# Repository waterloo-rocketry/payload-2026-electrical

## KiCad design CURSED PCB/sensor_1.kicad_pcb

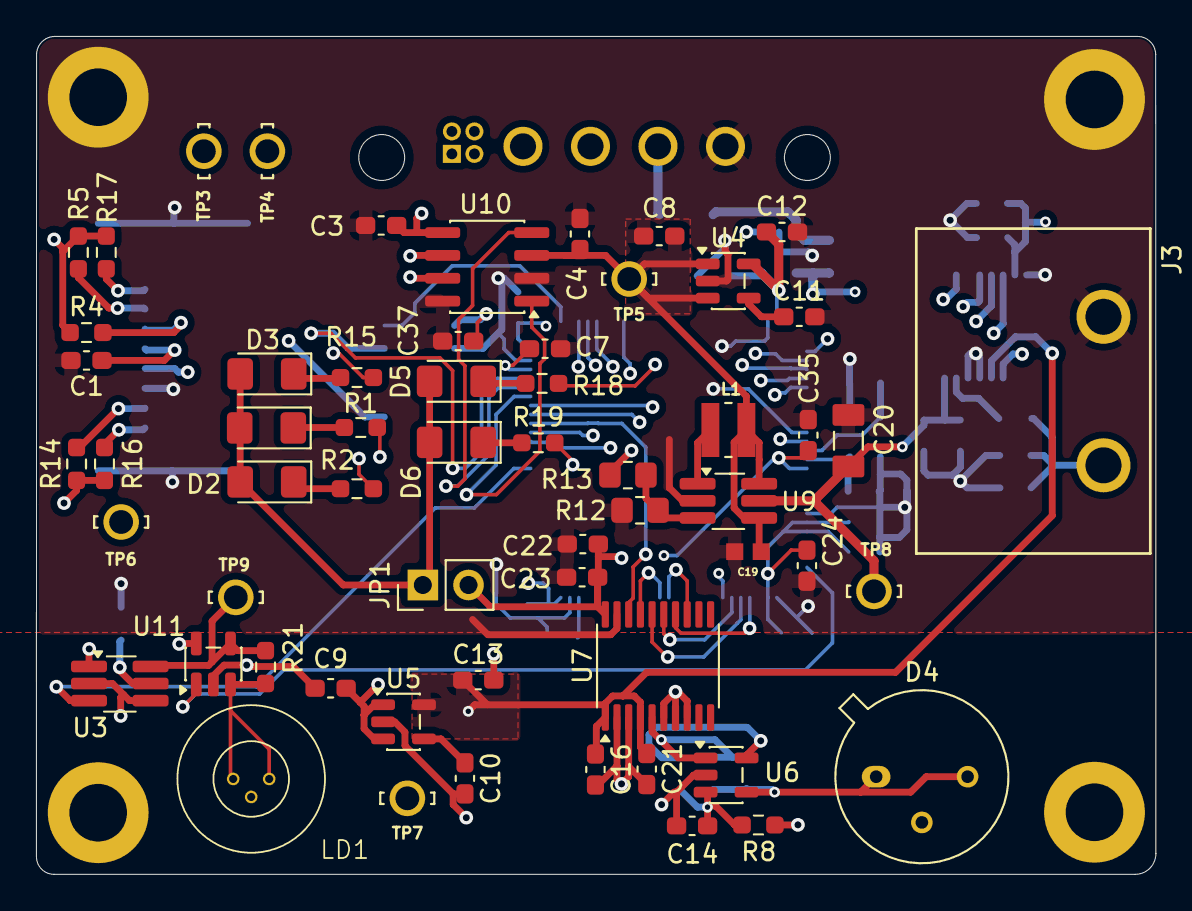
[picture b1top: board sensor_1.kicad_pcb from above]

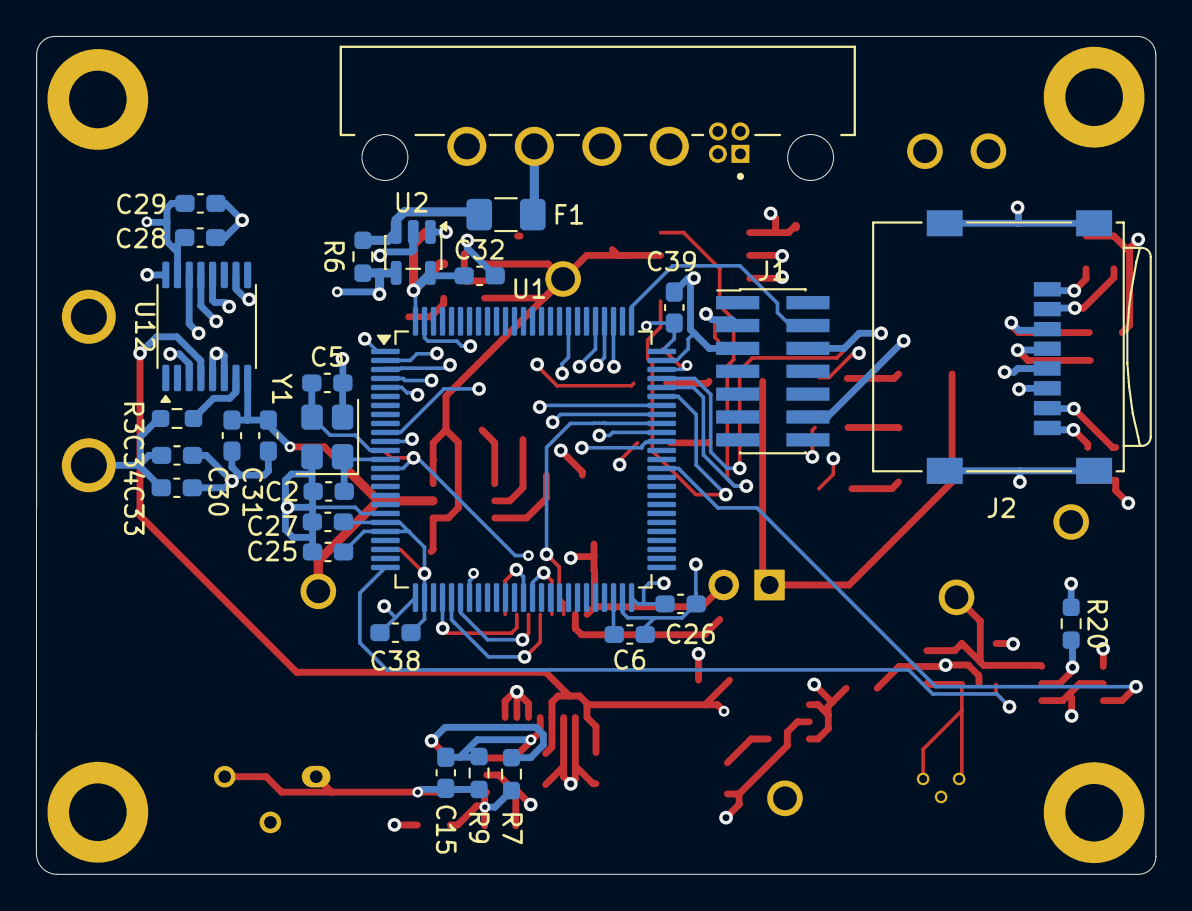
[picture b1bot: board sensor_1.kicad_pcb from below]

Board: 4 copper layers, 62.2 x 46.5 mm, 92 parts (29 on the bottom side), 58 nets.

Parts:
C1, C3, C4, C16, C22, C32: 0.1uF; C_0603_1608Metric_Pad1.08x0.95mm_HandSolder
C2, C5: 6pF; C_0603_1608Metric_Pad1.08x0.95mm_HandSolder
C6, C7: 2.2uF; C_0603_1608Metric_Pad1.08x0.95mm_HandSolder
C8, C9, C12, C13, C25, C26, C27, C35, C37, C38, C39: 1uF; C_0603_1608Metric_Pad1.08x0.95mm_HandSolder
C10, C11: 10nF; C_0603_1608Metric_Pad1.08x0.95mm_HandSolder
C14: 0.1u; C_0603_1608Metric_Pad1.08x0.95mm_HandSolder
C15: 6500nF; C_0603_1608Metric_Pad1.08x0.95mm_HandSolder
C19: 1uF; CAPC1608X90N
C20: 4.75uF; CAPC3216X180N
C21, C23, C29, C31, C34: 10uF; C_0603_1608Metric_Pad1.08x0.95mm_HandSolder
C24: 4.7uF; C_0603_1608Metric_Pad1.08x0.95mm_HandSolder
C28, C30: 100nF; C_0603_1608Metric_Pad1.08x0.95mm_HandSolder
C33: 100uF; C_0603_1608Metric_Pad1.08x0.95mm_HandSolder
D1, D3, D5, D6: BLUE LED; LED_1206_3216Metric_Pad1.42x1.75mm_HandSolder
D2: RED LED; LED_1206_3216Metric_Pad1.42x1.75mm_HandSolder
D4: ODD-5WISOL; TO-5-3
F1: 1A; Fuse_1206_3216Metric_Pad1.42x1.75mm_HandSolder
H1: MH1; MountingHole_3.2mm_M3_DIN965_Pad
H2: MH2; MountingHole_3.2mm_M3_DIN965_Pad
H3: MH3; MountingHole_3.2mm_M3_DIN965_Pad
H4: MH4; MountingHole_3.2mm_M3_DIN965_Pad
J1: Debugging Connector; PinHeader_2x07_P1.27mm_Vertical_SMD
J2: Micro_SD_Card; microSD_Molex_WM6698CT-ND
J3: Conn_01x02_Pin; BarrierBlock_ED2945-ND
J5: G125-MH104M4-04AD000P; connector_Harwin_G125-MH104M4-04AD000P
JP1: Jumper; PinHeader_1x02_P2.54mm_Vertical
L1: VLS3012CX-100M-1; IND_VLS3012CX-100M-1
LD1: D_Laser_Photo_PType; L840P200
R1, R2, R15, R18, R19: 220R; R_0603_1608Metric_Pad0.98x0.95mm_HandSolder
R3: 0R; R_0603_1608Metric_Pad0.98x0.95mm_HandSolder
R4, R5, R14, R16, R17: 10k; R_0603_1608Metric_Pad0.98x0.95mm_HandSolder
R6, R21: 33m; R_0603_1608Metric_Pad0.98x0.95mm_HandSolder
R7: 13.7k; R_0603_1608Metric_Pad0.98x0.95mm_HandSolder
R8: 280; R_0603_1608Metric_Pad0.98x0.95mm_HandSolder
R9: 128; R_0603_1608Metric_Pad0.98x0.95mm_HandSolder
R12: 71.5K; R_0805_2012Metric_Pad1.20x1.40mm_HandSolder
R13: 2.76M; R_0805_2012Metric_Pad1.20x1.40mm_HandSolder
R20: CALCUATE; R_0603_1608Metric_Pad0.98x0.95mm_HandSolder
TP3, TP4, TP5, TP6, TP7, TP8, TP9: 4952; KEYSTONE_4952
U1: STM32H750VBT6TR; LQFP-100_14x14mm_P0.5mm
U2, U11: INA180-A3; SOT-23-5
U3: AP22653AW6-7; TSOT-23-6_HandSoldering
U4, U5: SPX3819M5-L-3-3; SOT-23-5
U6: OPA323; SOT-23-5
U7: MCP3562-E_ST; TSSOP-20_4.4x6.5mm_P0.65mm
U9: TLV61046ADBVR; TSOT-23-6_HandSoldering
U10: MCP2562; SOIC-8_3.9x4.9mm_P1.27mm
U12: AD5761BRUZ; TSSOP-16_4.4x5mm_P0.65mm
Y1: 24MHz crystal; Crystal_SMD_Abracon_ABM8G-4Pin_3.2x2.5mm

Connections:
+3.3VA: C13.1, C16.1, C21.1, TP7.TP, U3.1 (IN), U5.5 (OUT), U7.1 (AVDD), U7.4 (REFIN+), U11.5 (V+), U12.4 (VREFIN)
+3.3VD: C1.1, C3.2, C12.1, C22.1, C23.1, C24.2, C25.2, C26.2, C27.2, C28.2, C29.2, C32.1, C37.2, C38.2, C39.2, J1.3, J2.4 (VDD), JP1.2 (B), R4.1, R5.1, R14.1, R16.1, R17.1, TP6.TP, U1.11 (VDD), U1.20 (VREF+), U1.21 (VDDA), U1.27 (VDD), U1.50 (VDD), U1.75 (VDD), U1.100 (VDD), U2.5 (V+), U4.5 (OUT), U7.20 (DVDD), U10.5 (VIO), U12.15 (DVCC)
+5V: C4.1, C8.1, C9.1, C19.1, L1.1, R6.2, R7.2, TP5.TP, U2.4 (-), U4.1 (IN), U4.3 (EN), U5.1 (IN), U5.3 (EN), U6.5 (V+), U9.4 (EN), U9.6 (VIN), U10.3 (VDD)
+24V: C20.1, C30.2, C31.2, R13.2, TP8.TP, U9.5 (VOUT), U12.8 (VDD)
/CS_ADC: U1.38 (PE8), U7.13 (~CS)
/CUR_SEN: U1.32 (PC4), U2.1
/IRQ/MDAT: U1.39 (PE9), U7.17 (~IRQ/MDAT)
/LAS_SENSE: U1.25 (PA3), U11.1
/Laser/Las_enable: U1.62 (PD15), U3.3 (EN/*EN)
/MCLR: C35.2, J1.12, U1.14 (NRST)
/MCU/CS_DAC: U1.69 (PA10), U12.13 (~SYNC)
/MCU/DAC_RESET: U1.68 (PA9), U12.3 (~RESET)
/MCU/OCS1/CLKIN: C5.1, U1.12 (PH0-OSC_IN), Y1.3
/MCU/OCS2/CLKOUT: C2.2, U1.13 (PH1-OSC_OUT), Y1.1
/MISO: U1.30 (PA6), U7.16 (SDO), U12.12 (SDI)
/MKLKIN: U1.67 (PA8), U7.18 (MCLKIN)
/MOSI: U1.31 (PA7), U7.15 (SDI), U12.10 (SDO)
/PGC/ICSPDAT: J1.4, U1.76 (PA14)
/PGD/ICSPCLK: J1.6, U1.72 (PA13)
/PZT: C33.2, C34.2, J3.1, R3.2
/Power/CANH: J5.1 (CANH), TP3.TP, U10.7 (CANH)
/Power/CANL: J5.2 (CANL), TP4.TP, U10.6 (CANL)
/RXD: U1.71 (PA12), U10.4 (RXD)
/SCLK: U1.29 (PA5), U7.14 (SCK), U12.14 (SCLK)
/SD_CS: J2.3 (CMD), R4.2, U1.83 (PD2)
/SD_DATA0: J2.7 (DAT0), R14.2, U1.65 (PC8)
/SD_DATA1: J2.8 (DAT1), R16.2, U1.66 (PC9)
/SD_DATA2: J2.1 (DAT2), R17.2, U1.78 (PC10)
/SD_DATA3: J2.2 (DAT3/CD), R5.2, U1.79 (PC11)
/SD_SCLK: J2.5 (CLK), U1.80 (PC12)
/TXD: U1.70 (PA11), U10.1 (TXD)
GND: C1.2, C2.1, C3.1, C4.2, C5.2, C6.1, C7.1, C8.2, C9.2, C10.2, C11.2, C12.2, C13.2, C14.1, C16.2, C19.2, C20.2, C21.2, C22.2, C23.2, C24.1, C25.1, C26.1, C27.1, C28.1, C29.1, C30.1, C31.1, C32.2, C33.1, C34.1, C35.1, C37.1, C38.1, C39.1, D4.2 (A), H1.1 (1_1), H2.1 (1_1), H3.1 (1_1), H4.1 (1_1), J1.5, J2.6 (VSS), J2.9 (SHIELD), J3.2, J5.D (GND), LD1.3, R8.2, R12.1, R20.1, U1.10 (VSS), U1.19 (VSSA), U1.26 (VSS), U1.49 (VSS), U1.74 (VSS), U1.99 (VSS), U2.2 (GND), U3.2 (GND), U3.4 (*FAULT), U4.2 (GND), U5.2 (GND), U6.2 (V-), U7.2 (AGND), U7.3 (REFIN-), U7.6 (CH1), U7.7 (CH2), U7.8 (CH3), U7.19 (DGND), U9.2 (GND), U10.2 (VSS), U10.8 (STBY), U11.2 (GND), U12.5 (AGND), U12.6 (VSS), U12.16 (DGND), Y1.2, Y1.4
unnamed: D1.2 (A), D2.2 (A), D3.2 (A), D5.2 (A), D6.2 (A), JP1.1 (A)
unnamed: D1.1 (K), R1.1
unnamed: D2.1 (K), R2.1
unnamed: D3.1 (K), R15.1
unnamed: C15.1, D4.1 (K), D4.3 (Cathode_2), R9.1, U6.4 (-)
unnamed: D5.1 (K), R18.1
unnamed: D6.1 (K), R19.1
unnamed: F1.1, J5.C (+5V)
unnamed: R2.2, U1.1 (PE2)
unnamed: R1.2, U1.2 (PE3)
unnamed: R18.2, U1.3 (PE4)
unnamed: R15.2, U1.4 (PE5)
unnamed: R19.2, U1.5 (PE6)
unnamed: C6.2, U1.48 (VCAP1)
unnamed: C7.2, U1.73 (VCAP2)
unnamed: F1.2, R6.1, U2.3 (+)
unnamed: R20.2, U3.5 (ILIM)
unnamed: C11.1, U4.4 (BP)
unnamed: C10.1, U5.4 (BP)
unnamed: C14.2, R7.1, R8.1, U6.3 (+)
unnamed: C15.2, R9.2, U6.1, U7.5 (CH0)
unnamed: R12.2, R13.1, U9.3 (FB)
unnamed: L1.2, U9.1 (SW)
unnamed: LD1.1, LD1.2, R21.2, U11.3 (+)
unnamed: R21.1, TP9.TP, U3.6 (OUT), U11.4 (-)
unnamed: R3.1, U12.7 (VOUT)

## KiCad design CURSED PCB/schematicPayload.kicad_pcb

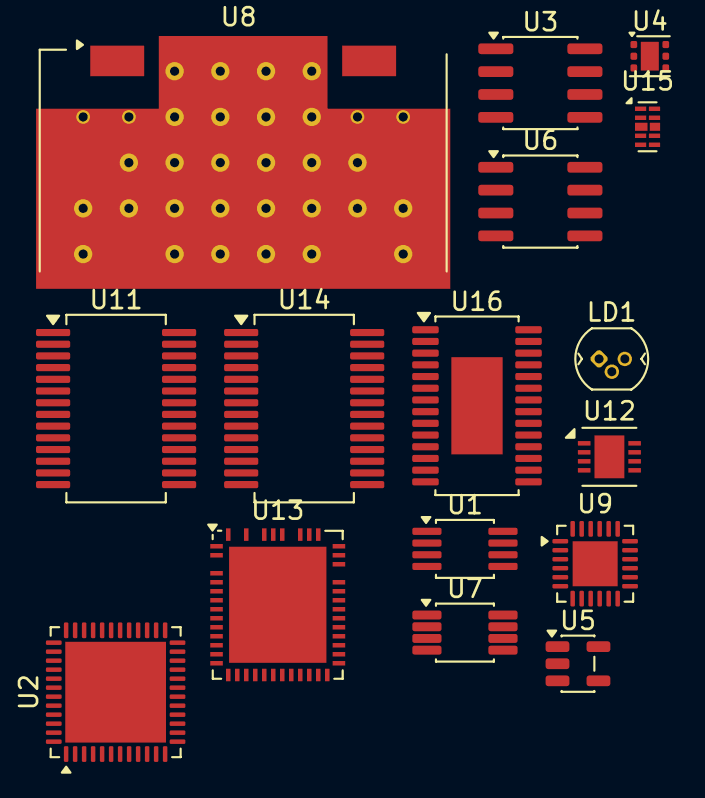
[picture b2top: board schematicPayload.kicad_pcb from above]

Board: 2 copper layers, 16 parts (0 on the bottom side), 22 nets, no tracks yet.

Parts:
LD1: PL520; LaserDiode_TO38ICut-3
U1: LT1962-3.3; MSOP-8_3x3mm_P0.65mm
U2: STM32F401CBUx; QFN-48-1EP_7x7mm_P0.5mm_EP5.6x5.6mm
U3: OPA847xD; SOIC-8_3.9x4.9mm_P1.27mm
U4: TVS0500DRV; WSON-6-1EP_2x2mm_P0.65mm_EP1x1.6mm
U5: LM4132xMF-1.8; SOT-23-5
U6: BUF602xD; SOIC-8_3.9x4.9mm_P1.27mm
U7: ADC082S021; VSSOP-8_3x3mm_P0.65mm
U8: LPF-B0R3; Mini-Circuits_HZ1198_LandPatternPL-247
U9: iC-HTG; HVQFN-24-1EP_4x4mm_P0.5mm_EP2.5x2.5mm
U11: AD9850; SSOP-28_5.3x10.2mm_P0.65mm
U12: LTC6102HVxDD; DFN-8-1EP_3x3mm_P0.5mm_EP1.66x2.38mm
U13: LTC3886; Linear_UGK52_QFN-46-52
U14: CY7C65213-28PVXI; SSOP-28_5.3x10.2mm_P0.65mm
U15: ESD224DQA; Diodes_UDFN-10_1.0x2.5mm_P0.5mm
U16: MAX1968xUI; HTSSOP-28-1EP_4.4x9.7mm_P0.65mm_EP2.85x5.4mm

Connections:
unnamed: U1.5 (~SHDN), U1.8 (IN), U13.47 (Iin+)
unnamed: U3.2 (-), U3.3 (+)
unnamed: U4.4 (IN), U4.5 (IN), U4.6 (IN)
unnamed: U4.1 (GND), U4.2 (GND), U4.3 (GND), U4.7 (GND)
unnamed: LD1.1 (A), U9.23 (VDD)
unnamed: U16.6 (LX2), U16.8 (LX2), U16.10 (LX2)
unnamed: U1.3 (BYP), U1.4 (GND), U2.24 (VDD), U3.7 (V+), U7.2 (V_{A}), U8.3 (GND), U8.4 (GND), U8.5 (GND), U8.6 (GND), U9.24 (VB), U11.5 (DGND), U12.7 (V+), U16.1 (VDD)
unnamed: U1.1 (OUT), U1.2 (SENSE)
unnamed: U2.10 (PA0), U7.7 (DOUT)
unnamed: U2.5 (PH0), U9.11 (MCL)
unnamed: U2.23 (VSS), U2.35 (VSS), U2.47 (VSS), U2.49 (VSS)
unnamed: U5.5 (VREF), U6.5 (V-)
unnamed: U7.5 (IN1), U8.2 (OUT)
unnamed: U3.6, U8.1 (IN)
unnamed: U9.20 (GND), U9.25 (GND)
unnamed: U11.10 (AGND), U11.19 (AGND)
unnamed: U11.11 (AVDD), U11.18 (AVDD)
unnamed: U2.28 (PB15), U11.1 (D3)
unnamed: U11.20 (IOUTB), U12.1 (-INS)
unnamed: U15.3 (VSS), U15.8 (VSS)
unnamed: U16.18 (PVDD1), U16.20 (PVDD1)
unnamed: U16.9 (PVDD2), U16.11 (PVDD2)

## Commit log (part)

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2025-11-08 Test
2025-11-08 November 8, 2025
2025-11-12 Add files via upload
    new connections
2025-11-12 added stuff
2025-11-14 Removed Laser output
    There was a random laser output deleted it off the schematic to make it cleaner
2025-11-23 Added amplifer parts for photoelectric diode
2025-11-24 Updated PCB compoments
2025-11-24 updated custom footprints
2025-11-24 Backup files for senor kicad
2025-11-24 Added some amplifer stuff
2025-11-26 Updates to PCB before exam sesaon
    idk what I added ngl
2026-01-05 Added values for schematic
2026-01-07 Added pre-verison to finished PCB
2026-01-09 Added reference voltage and some other stuff
2026-01-10 Fixes to schematic
2026-01-21 Create fpga boards
2026-01-21 Create something
2026-01-29 Changes to stuff
2026-01-30 Add .gitignore for KiCad and temporary files
2026-01-30 Initialize .gitignore with project-specific rules
    Add common file patterns to .gitignore for KiCad projects and temporary files.
2026-01-30 fixed issue with mcu
2026-01-31 something something footprints
2026-01-31 something something fixes to something related
2026-02-03 fixed errors
2026-02-03 changes to something
2026-02-03 something related to current and stuff
2026-02-03 forgot to rename things
2026-02-05 some fixes to conner critique
2026-02-07 Small changes
2026-02-11 file
2026-02-11 i hope this dont break git
2026-02-11 measure
2026-02-11 more light
2026-02-11 name
2026-02-11 wire
2026-02-13 slep
2026-02-14 haley fpga thing
2026-02-14 moved fpga to another brnach
2026-02-17 connected stuff for pcb
2026-02-18 i am a LED
2026-02-19 small error
2026-02-22 redone pcb
2026-02-22 wires
2026-02-22 no spilt-ground plane (bad idea)
2026-02-23 adressing koby thing
2026-02-23 grounding stuff
2026-02-23 smell error
2026-02-23 adressing conner fixes
2026-02-25 fixes to experimental problems
2026-02-25 added path thorugh for gdn
2026-02-26 Add files via upload
    Replaced original fpga with ICE40UP5K
    - connected U2B ADC
    - connected U2D to voltage supply
    - U2A/C connected but floating for now
    Removed original DAC -> to be replaced with DAC of higher voltage
    Removed wiring from CH on ADC
2026-02-27 3/4 revisons done from darian
2026-02-27 fixes from darian review
2026-02-27 small fix
2026-03-01 Fixes to pranav sugestions
2026-03-03 fix with ash
2026-03-03 component fixes
2026-03-03 smell fix
2026-03-03 darian fices
2026-03-03 push
2026-03-04 text for reviwers
2026-03-04 added some pass throughs
2026-03-04 added laser warning
2026-03-04 clearance
2026-03-05 moved text
2026-03-05 conner
2026-03-08 updated schematic
2026-03-10 kicad
2026-03-10 schematic changes
2026-03-10 title change
2026-03-10 title back
2026-03-10 schematic and layout changes
2026-03-10 upcate
2026-03-10 footprint folde rupdate
2026-03-10 temp circuit update
2026-03-10 updates traces and footprints
2026-03-10 drc errors
2026-03-10 updated booster
2026-03-13 cleaned upa trace
2026-03-13 Create IOC file
2026-03-13 Updated PDF and make schematic look more pretty
2026-03-14 fixed broken commit?
2026-03-14 updated misiing datasheet rdy for review
2026-03-14 Rewording schematic text
2026-03-17 extra cleanup while waiting for review
2026-03-17 added a warning label
2026-03-17 fixed some odd looking vias
2026-03-17 fixed cursense
2026-03-17 small traces redoes
2026-03-17 moved warning label slighty
2026-03-17 cleaned up a a long trace
2026-03-17 last change trust
2026-03-17 commit for pranav
2026-03-18 forgot to commit
2026-03-18 ready for review
2026-03-18 moved around power planes for better coverage, rdy for review
2026-03-18 added title for board
2026-03-18 fixes from ash review
2026-03-19 im not sure what this is or what changed
2026-03-25 Add files via upload
    Added SPI Flash, decoupling capacitors to ADC, decoupling to FPGA power pins and VCCPLL,
